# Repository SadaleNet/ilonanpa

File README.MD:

# Ilo Nanpa - Toki Pona Numeral Calculator

(sina sona e toki pona, la o tawa lipu [https://ilonanpa.sadale.net/](https://ilonanpa.sadale.net/). mi kepeken toki ike tan ni: nimi sona "Programming" li ike. toki ike Inli taso li lon lipu ni.)

Ilo Nanpa is a hardware calculator designed for Toki Pona Numeral. [Toki Pona](http://tokipona.org/) is a minimalist constructed language designed by jan Sonja with an obscure, non-base-10 numeral system.

This repository contains the source code of the firmware as well as the source files of hardware design. This readme file mainly describes the procedure of building the firmware as well as working with factory mode. For the usage of this device and other technical details, please refer to [the official English blogpost of Ilo Nanpa on sadale.net](https://sadale.net/58/).

# Repository Structure

* src/ - source code of the firmware
* pcb/ - KiCad hardware design files
* bin/ - Compiled source code (generated after running Makefile)

# Microcontroller

The microcontroller of this project is STM8S001J3.

# Dependencies

* Make (for Makefile)
* Compiler: sdcc
* Firmware uploading tool: stm8flash, to be used with stlinkv2.
* PCB Software: KiCad (for modification of hardware design. It isn't needed for firmware development)

# Building and Flashing the Firmware

* Run `make` to build the firmware.

* Connect stlink with Ilo Nanpa. On the backside of the device, there's a 3-pin male header on the top-left corner. The pin 1 is Vcc, pin 2 is ground and pin 3 is SWIM.

* Run `make flash-opt-bytes` to flash the option bytes (fusebit-like configuration). It maps ADC channel 2 to the ala-wan-tu button group. This operation only need to be performed once for each microcontroller. For some reason, the first run returns me an error. I have to run this command twice to get it work.

* Run `make flash` to upload the firmware to the microcontroller. For some reason, the first run of the command often fails. Perhaps it has something to do with clock configuration. I have to run this command twice to get it uploaded.

# Reprogramming the Device

To reprogram the device, hold the "pana" button before powering up the device. This prevents the device from leaving programming mode. As soon as "pana" is released, the device would leave programming mode and enter normal operation mode.

# Factory Mode

Due to the design of the device, ADC calibration procedure has to be performed for getting the button detection of the device work. This can be performed using factory mode. In addition, factory mode is able to perform key tests and LED brightness adjustment.

** If you're a holder of Ilo Nanpa and you have no idea on what this mode does, please do NOT enter factory mode. This mode would cause your device not to be able to properly detect key presses if it isn't used properly. **

Please ensure that you aren't touching any LEDs or resistors with your fingers during the process.

To enter factory mode:

1. Hold down the "ala" button and power the device on.

2. Wait for 5 seconds. The LEDs suno9,10,11,12 would turn on.

3. Press the buttons in the following sequence. ala, pana, luka, pana, ala, luka, luka, pana. If you press any of them wrong, the firmware would enter normal mode and would not enter factory mode.

4. Slide the en/weka slider switch to `en` position.

5. The LEDs suno1 and suno12 should light up. If suno8 is also lit, you're too slow and you have to slide the en/weka slider to `weka` position and back to `en` position again.

6. You're now in ADC calibration scene. Press the buttons in this sequence for 5 times: ala, wan, tu, luka, mute, ali, pana, kama, tenpo. This calibrates the ADC values when the slider is in `en` position. After this step, the ADC calibration values are saved to the EEPROM.

7. The LEDs suno1,8,12 should be lit. You've entered key test scene. The buttons are grouped as shown below:

	* suno1,2,3,4 <=> RELEASED,ala,wan,tu
	* suno8,9,10,11 <=> RELEASED,luka,mute,ali
	* suno12,13,14,15 <=> RELEASED,pana,kama,tenpo

	For example, when ala is pressed, suno2 would be lit. When wan is pressed, suno3 would be lit. When tu is pressed, suno4 would be lit. When none of ala, wan and tu is pressed, suno1 would be lit.

8. Repeat step 4 to 7, but with slider switch positioned at `weka` instead of `en`.

9. If you're in key test scene, you can enter brightness adjustment scene. To enter brightness adjustment scene, hold ala, luka and tenpo at the same time.

10. The higher the maxActionCount, the lower the brightness. In brightness adjustment scene, press wan to reduce maxActionCount by 10, tu to reduce maxActionCount by 1, mute to increase maxActionCount by 1, ali to increase maxActionCount by 10. The number shown on the LEDs is the current maxActionCount in Toki Pona Numeral.

11. To get back to key test scene from brightness adjustment scene, hold ala, luka and tenpo at the same time. To get back to ADC calibration scene, slide the slider switch in any scene.

# Working with Hardware Design
Just open up `pcb/ilonanpa.pro` with KiCad. The documentation of KiCad can be found on their website.

Please notice that unusual electronic designator is being used. Instead of R1, R2, R3 for resistors, we have awen1, awen2, awen3. It's designed in this way because this device is designed to have Toki Pona culture in mind. In case you're confused, please refer to the electronic symbol.

# License
This project is licensed under BSD 2-clause license.

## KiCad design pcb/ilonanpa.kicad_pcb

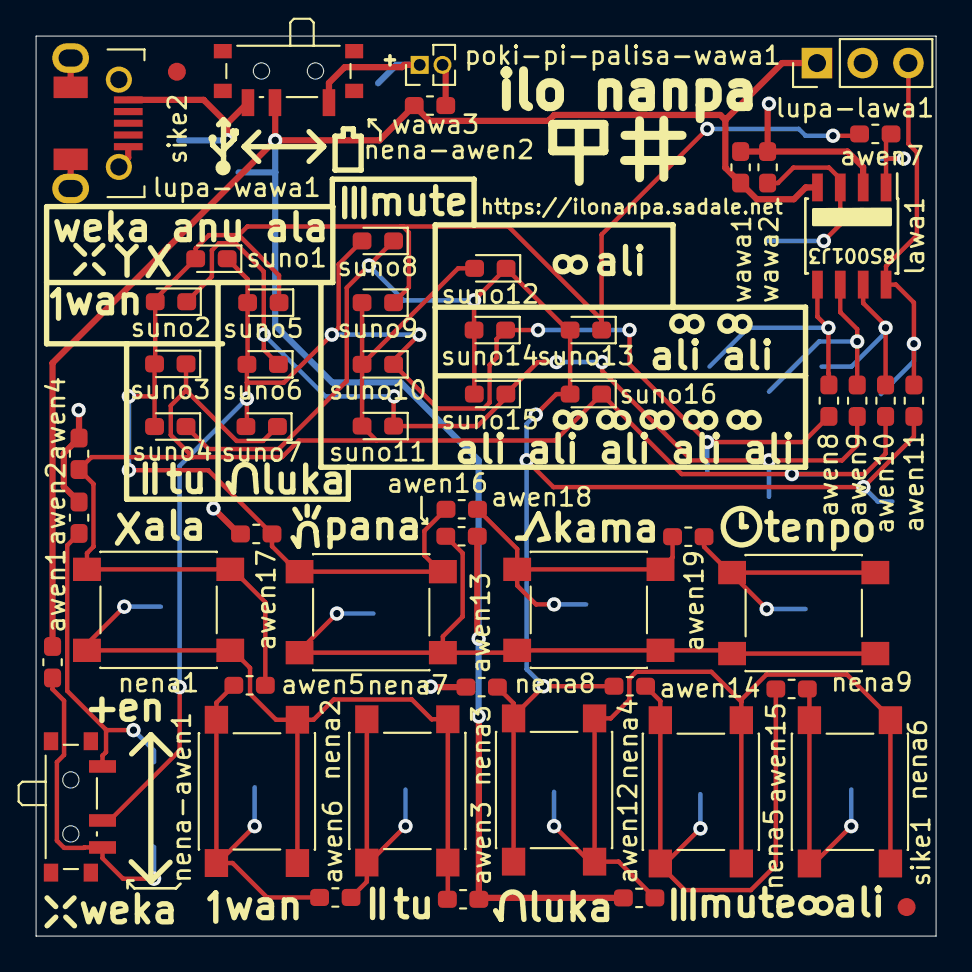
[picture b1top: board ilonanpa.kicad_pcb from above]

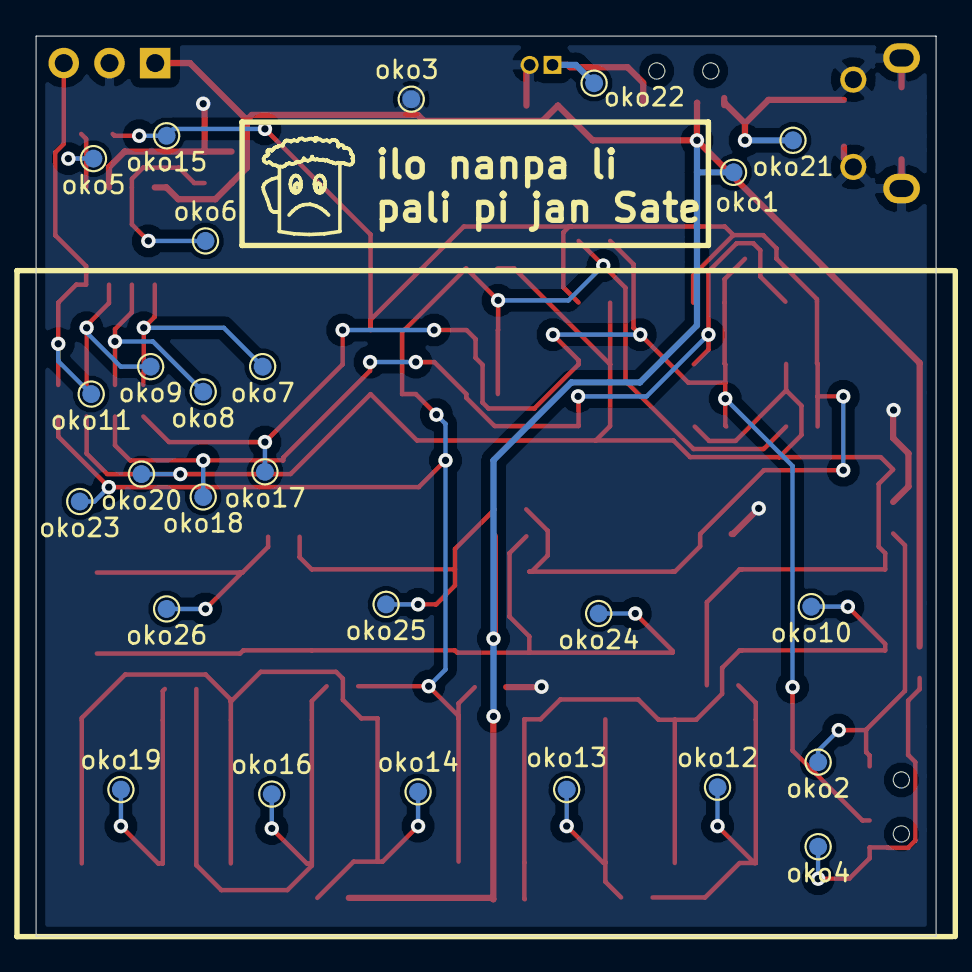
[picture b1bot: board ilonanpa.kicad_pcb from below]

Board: 2 copper layers, 50.0 x 50.0 mm, 81 parts (26 on the bottom side), 26 nets.

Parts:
awen1, awen2, awen4, awen13, awen17: 470k; R_0603_1608Metric_Pad1.05x0.95mm_HandSolder
awen3, awen12, awen16: 10k; R_0603_1608Metric_Pad1.05x0.95mm_HandSolder
awen5, awen6, awen14, awen15, awen18, awen19: 20k; R_0603_1608Metric_Pad1.05x0.95mm_HandSolder
awen7, awen8, awen9, awen10, awen11: 120; R_0603_1608Metric_Pad1.05x0.95mm_HandSolder
lawa1: STM8S001J3; SOIC-8_3.9x4.9mm_P1.27mm
lupa-lawa1: lupa lawa; PinHeader_1x03_P2.54mm_Vertical
lupa-wawa1: USB_B_Micro; USB_Micro-B_A01SB141B1-067
nena1: ala; SW_SPST_PTS645
nena2: wan; SW_SPST_PTS645
nena3: tu; SW_SPST_PTS645
nena4: luka; SW_SPST_PTS645
nena5: mute; SW_SPST_PTS645
nena6: ali; SW_SPST_PTS645
nena7: pana; SW_SPST_PTS645
nena8: kama; SW_SPST_PTS645
nena9: tenpo; SW_SPST_PTS645
nena-awen1: en anu weka; SW_SPDT_PCM12
nena-awen2: ante wawa; SW_SPDT_PCM12
oko1, oko2, oko3, oko4, oko5, oko6, oko7, oko8, oko9, oko10, oko11, oko12, oko13, oko14, oko15, oko16, oko17, oko18, oko19, oko20, oko21, oko22, oko23, oko24, oko25, oko26: oko; TestPoint_Pad_D1.0mm
poki-pi-palisa-wawa1: wawa palisa "AAA" tu wan; PinHeader_1x02_P1.27mm_Vertical
sike1, sike2: Fiducial_1mm_Dia_2mm_Outer
suno1: weka anu ala; LED_0603_1608Metric_Pad1.05x0.95mm_HandSolder
suno2: wan; LED_0603_1608Metric_Pad1.05x0.95mm_HandSolder
suno3, suno4: tu; LED_0603_1608Metric_Pad1.05x0.95mm_HandSolder
suno5, suno6, suno7: luka; LED_0603_1608Metric_Pad1.05x0.95mm_HandSolder
suno8, suno9, suno10, suno11: mute; LED_0603_1608Metric_Pad1.05x0.95mm_HandSolder
suno12: ali; LED_0603_1608Metric_Pad1.05x0.95mm_HandSolder
suno13, suno14: ali ali; LED_0603_1608Metric_Pad1.05x0.95mm_HandSolder
suno15, suno16: ali ali ali ali ali; LED_0603_1608Metric_Pad1.05x0.95mm_HandSolder
wawa1: 100n; C_0603_1608Metric_Pad1.05x0.95mm_HandSolder
wawa2: 2u2; C_0603_1608Metric_Pad1.05x0.95mm_HandSolder
wawa3: 10u; C_0603_1608Metric_Pad1.05x0.95mm_HandSolder

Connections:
/1: awen7.2, lawa1.1, oko5.1
/5: awen8.2, lawa1.5, oko7.1
/6: awen9.2, lawa1.6, oko8.1
/7: awen10.2, lawa1.7, oko9.1
/8: awen11.2, lawa1.8, lupa-lawa1.3, oko11.1
/A: awen7.1, awen17.2, awen18.1, nena7.2, oko15.1, suno1.2, suno2.2, suno3.2, suno4.2, suno5.1, suno9.1, suno13.1
/AIN2: awen4.2, awen5.1, awen10.1, nena1.2, oko20.1, suno3.1, suno7.1, suno9.2, suno10.2, suno11.2, suno12.2, suno16.1
/AIN4,5: awen11.1, awen13.2, awen14.1, nena4.2, oko23.1, suno4.1, suno8.1, suno12.1, suno13.2, suno14.2, suno15.2, suno16.2
/B: awen8.1, nena-awen1.2, oko17.1, suno1.1, suno5.2, suno6.2, suno7.2, suno8.2, suno10.1, suno14.1
/C: awen9.1, oko18.1, suno2.1, suno6.1, suno11.1, suno15.1
GND: awen2.2, awen4.1, awen13.1, awen17.1, lawa1.2, lupa-lawa1.2, lupa-wawa1.5, lupa-wawa1.6, oko3.1, poki-pi-palisa-wawa1.2, wawa1.1, wawa2.1, wawa3.2
unnamed: awen1.2, nena-awen1.3, oko4.1
unnamed: awen2.1, nena-awen1.1, oko2.1
unnamed: awen3.2, nena1.1, nena2.1, nena3.1, oko10.1
unnamed: awen5.2, awen6.1, nena2.2, oko12.1
unnamed: awen6.2, nena3.2, oko13.1
unnamed: awen12.2, nena4.1, nena5.1, nena6.1, oko14.1
unnamed: awen14.2, awen15.1, nena5.2, oko16.1
unnamed: awen15.2, nena6.2, oko19.1
unnamed: awen16.2, nena7.1, nena8.1, nena9.1, oko24.1
unnamed: awen18.2, awen19.1, nena8.2, oko25.1
unnamed: awen19.2, nena9.2, oko26.1
unnamed: lawa1.3, oko6.1, wawa2.2
unnamed: lupa-wawa1.1, nena-awen2.3, oko21.1
unnamed: nena-awen2.1, oko22.1, poki-pi-palisa-wawa1.1
VDD: awen1.1, awen3.1, awen12.1, awen16.1, lawa1.4, lupa-lawa1.1, nena-awen2.2, oko1.1, wawa1.2, wawa3.1

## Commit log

2019-01-15 Fixed inconsistency between pin definition of LMA_PIN and ADC channel of BUTTON_LMA_CHANNEL
2019-01-15 Turns on ADC only when needed.
2019-01-15 Sharing the same internal pin for both input handling and output handling.
2019-01-15 Bugfix: The initial state of en/weka isn't detected on power on. Before this fix, if the user pressed a button in weka state right after power on, it would be regarded as en instead of weka.
